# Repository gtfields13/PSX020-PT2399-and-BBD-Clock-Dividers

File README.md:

# PSX020 PT2399 and BBD Clock Dividers

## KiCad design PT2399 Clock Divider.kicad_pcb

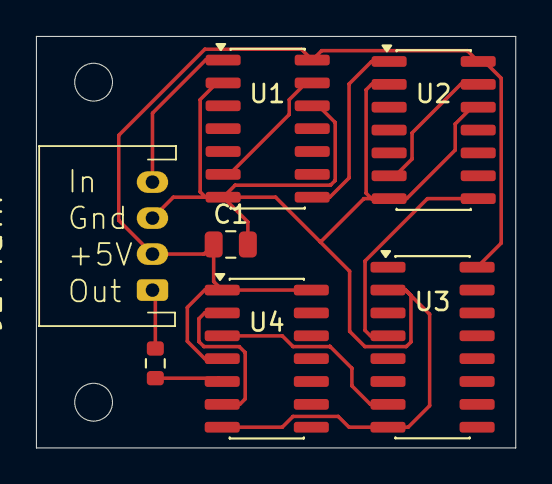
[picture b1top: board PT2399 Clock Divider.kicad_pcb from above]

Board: 2 copper layers, 26.6 x 22.9 mm, 7 parts (1 on the bottom side), 11 nets.

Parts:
C1: 0.1µF; C_0805_2012Metric
J1: Main; JST_PH_S4B-PH-K_1x04_P2.00mm_Horizontal
R1: 220R; R_0603_1608Metric
U1, U2: 74HC393M96; SOIC-14_3.9x8.7mm_P1.27mm
U3: 74HC390M96; SOIC-16_3.9x9.9mm_P1.27mm
U4: 74HC74; SOIC-14_3.9x8.7mm_P1.27mm

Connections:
+5V: C1.1, J1.2, U1.14 (VCC), U2.14 (VCC), U3.16 (VCC), U4.1 (~R), U4.4 (~S), U4.14 (VCC)
ClockIn: J1.4, U1.1 (*1CP)
GND: C1.2, J1.3, U1.2 (1MR), U1.7 (GND), U1.12 (2MR), U2.2 (1MR), U2.7 (GND), U2.12 (2MR), U3.2 (1MR), U3.8 (GND), U4.7 (GND)
unnamed: U1.8 (2Q3), U2.1 (*1CP)
unnamed: U1.6 (1Q3), U1.13 (*2CP)
unnamed: U2.8 (2Q3), U3.4 (*1CP1)
unnamed: U2.6 (1Q3), U2.13 (*2CP)
unnamed: U3.7 (1Q3), U4.3 (C)
unnamed: U4.2 (D), U4.6 (~Q)
unnamed: R1.1, U4.5 (Q)
PulseOut: J1.1, R1.2

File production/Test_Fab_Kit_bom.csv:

Designator,Footprint,Quantity,Value,LCSC Part #
C1,0805,1,0.1µF,C28233
J1,JST_PH_S4B-PH-K_1x04_P2.00mm_Horizontal,1,Main,
R1,0603,1,220R,C22962
"U1, U2",SOIC-14_3.9x8.7mm_P1.27mm,2,74HC393M96,C53114418
U3,SOIC-16_3.9x9.9mm_P1.27mm,1,74HC390M96,C53114298
U4,SOIC-14_3.9x8.7mm_P1.27mm,1,74HC74,C27597
